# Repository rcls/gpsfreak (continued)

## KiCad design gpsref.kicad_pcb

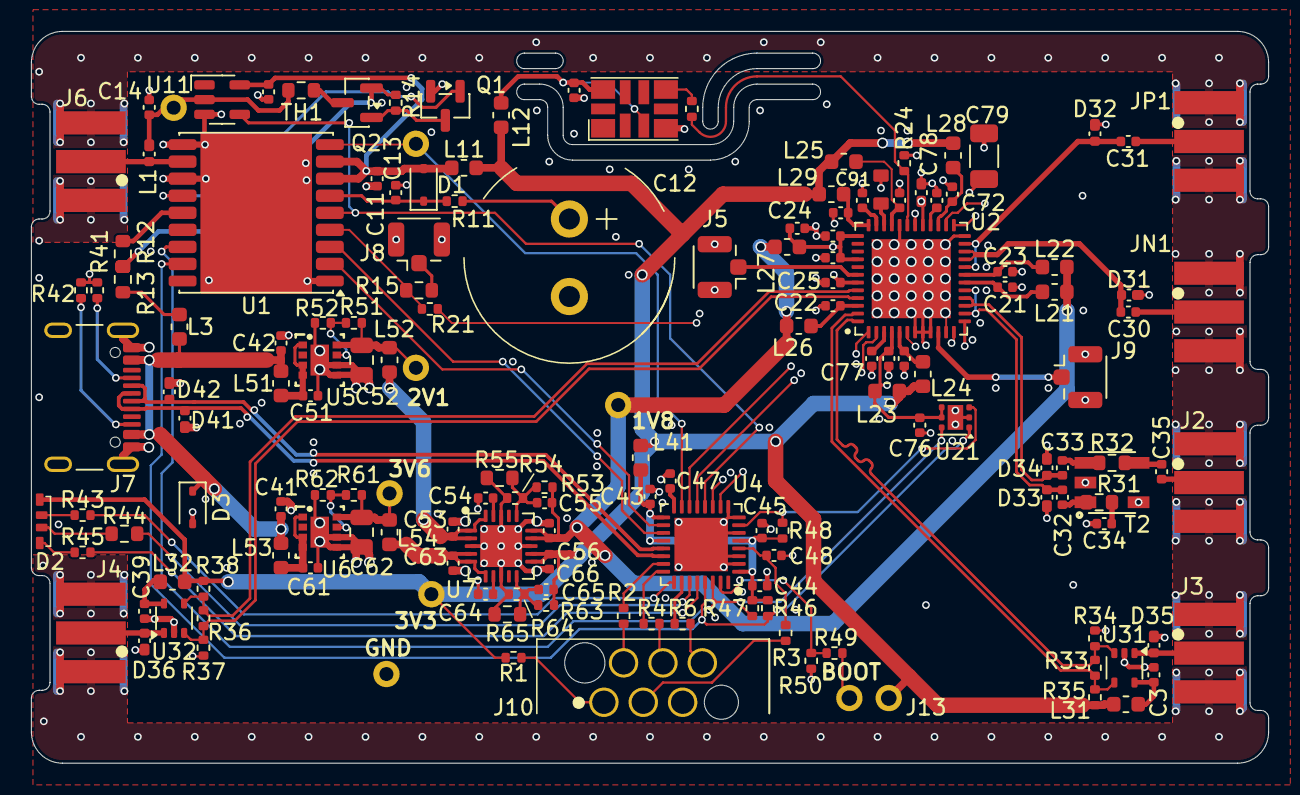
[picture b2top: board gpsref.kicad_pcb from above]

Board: 4 copper layers, 79.8 x 47.2 mm, 158 parts (0 on the bottom side), 102 nets.

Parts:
C3, C11, C21, C22, C23, C24, C29, C39, C43, C51, C53, C56, C61, C63, C66, C71, C72, C73, C74, C75, C77, C91, C93: 10u; C_0402_1005Metric
C12: .47F; CP_Radial_D13.5mm_P5.00mm
C13, C14, C15, C25, C27, C28, C30, C31, C32, C33, C35, C44, C45, C54, C64, C76: 0u1; C_0402_1005Metric
C34: 22p; C_0402_1005Metric
C41, C42: 1u; C_0402_1005Metric
C47: 4u7; C_0402_1005Metric
C48, C55, C65: 10n; C_0402_1005Metric
C52, C62: 47u; C_0805_2012Metric
C78: 10n; C_0402_1005Metric_Pad0.74x0.62mm_HandSolder
C79: 470n; C_1206_3216Metric
C92: 0u1; C0704
D1: 1N4148WS; D_SOD-323
D2: LED_GBAR; LED-QPLB615-RGB
D3: 5V6; D_SOD-323
D31, D32, D33, D34, D35, D36, D41, D42: D_TVS; HHS_0402
J2, J3, J4, J6: SMA; SMA_EdgeMount
J5, J8, J9: U.Fl; U.FL_Hirose_U.FL-R-SMT-1_Vertical
J7: USB_C_Receptacle_16P; USB_C_Receptacle_GCT_USB4105-xx-A_16P_TopMnt_Horizontal
J10: Skedd; Skedd6
J13: Boot; PinHeader_1x02_P2.54mm_Vertical
JN1: SMA; SMA_EdgeMount
JP1: SMA; SMA_EdgeMount
L1: 100n; HHS_0402
L3, L11, L12, L21, L22, L23, L24, L25, L26, L27, L28, L29, L31, L32, L41, L51, L52, L53, L54: 220; L_0603_1608Metric
Q1: AO3400A; SOT-23
Q2: AO3401A; SOT-23
R1, R2, R3, R4, R6, R11, R21, R23, R24, R33, R36, R49: 100; R_0402_1005Metric
R12, R13, R15, R32: 0; R_0603_1608Metric
R14, R34, R35, R37, R38, R50: 100k; R_0402_1005Metric
R31: 50; R_0603_1608Metric
R41, R42, R64: 5k1; R_0402_1005Metric
R43, R45: 1k; R_0402_1005Metric
R44: 2k7; R_0603_1608Metric
R46, R47, R48: 10k; R_0402_1005Metric
R51: 39k; R_0402_1005Metric
R52: 24k; R_0402_1005Metric
R53: 8k2; R_0402_1005Metric
R54: 7k5; R_0402_1005Metric
R55: 51k; R_0603_1608Metric
R61: 200k; R_0402_1005Metric
R62: 56k; R_0402_1005Metric
R63: 15k; R_0402_1005Metric
R65: 82k; R_0603_1608Metric
T2: MABA-010247-2R1250; XFMR_MABA-007159-000000
TH1: 220mA; R_0603_1608Metric
TP1, TP2, TP3, TP4, TP5, TP6, TP7: TestPoint_Probe; TestPoint
U1: MAX-M10S; ublox_MAX
U2: LMK05318BRGZR; QFN-48-1EP_7x7mm_P0.5mm_EP5.1x5.1mm
U3: TG5032CGN; QFN10_TG5032CGN 40.0000M-CAGHNA0_EPS
U4: STM32H503KBUx; QFN-32-1EP_5x5mm_P0.5mm_EP3.45x3.45mm
U5, U6: TPS82084SIL; SIL0008C_SMD_NV
U7: TPS7A8801RTJR; QFN-20-1EP_4x4mm_P0.5mm_EP2.7x2.7mm
U11: 74LVC1G07; SOT-23-5
U21: TMP117xxDRV; WSON-6-1EP_2x2mm_P0.65mm_EP1x1.6mm
U31, U32: TLV3601DCKR; SOT-353_SC-70-5

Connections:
+1V8: C55.1, C56.1, L21.1, L22.1, L26.1, L27.1, R53.1, TP6.1, U7.14 (OUT1), U7.15 (OUT1)
+3V3: C65.1, C66.1, D2.3 (A), J13.1, L11.1, L12.1, L23.1, L24.1, L25.1, L28.1, L29.1, L31.1, L32.1, L41.1, R1.2, R35.2, R38.2, R63.1, TP7.1, U7.11 (OUT2), U7.12 (OUT2)
/CPU/BOOT0: R49.2, R50.1, U4.31 (BOOT0)
/CPU/Blue: R43.2, U4.25 (USART3_RX)
/CPU/CC1: J7.A5 (CC1), R41.2
/CPU/CC2: J7.B5 (CC2), R42.2
/CPU/CPU_nRST: C48.1, R3.2, U4.4 (NRST)
/CPU/DBG_TX: R6.2, U4.26 (USART3_TX)
/CPU/Green: R44.2, U4.27 (PB4(NJTRST))
/CPU/Red: R45.2, U4.28 (PB5)
/CPU/SWCLK: R4.2, U4.24 (DEBUG_JTCK-SWCLK)
/CPU/SWDIO: R2.2, U4.23 (DEBUG_JTMS-SWDIO)
/CPU/USB_D+: D41.1 (A1), J7.A6 (D+), J7.B6 (D+), U4.22 (USB_DP)
/CPU/USB_D-: D42.1 (A1), J7.A7 (D-), J7.B7 (D-), U4.21 (USB_DM)
/CPU/VCPU: C43.1, C44.1, C45.1, L41.2, R46.2, R47.2, R48.2, U4.1 (VDD), U4.5 (VDDA), U4.17 (VDD), U4.20 (PA9)
/CPU/d3V3: J10.1, R1.1
/CPU/dBOOT: J13.2, R49.1
/CPU/dRST: J10.3, R3.1
/CPU/dSWC: J10.4, R4.1
/CPU/dSWD: J10.2, R2.1
/CPU/dTX: J10.6, R6.1
/Clocking/CAP_PLL1: C93.2, U2.28 (CAP_PLL1)
/Clocking/CAP_PLL2: C91.2, U2.35 (CAP_PLL2)
/Clocking/GPSCLKLO: R21.2, U2.6 (PRIREF_P)
/Clocking/LF1: C78.1, C79.1, U2.29 (LF1)
/Clocking/LF2: C92.1, U2.34 (LF2)
/Clocking/SecRef: J9.1 (In), U2.10 (SECREF_P)
/Clocking/VCC_XO: C29.1, L12.2, U3.3 (OE), U3.9 (VCC)
/Clocking/VDDO_01: C21.1, L21.2, U2.18 (VDDO_01)
/Clocking/VDDO_7: C22.1, L26.2, U2.46 (VDDO_7)
/Clocking/VDDO_23: C23.1, L22.2, U2.19 (VDDO_23)
/Clocking/VDDO_456: C24.1, C25.1, C27.1, C28.1, L27.2, U2.37 (VDDO_4), U2.40 (VDDO_5), U2.43 (VDDO_6)
/Clocking/VDDO_PLL2: C74.1, L29.2, U2.36 (VDD_PLL2)
/Clocking/VDDO_XO: C75.1, L25.2, U2.33 (VDD_XO)
/Clocking/VDD_DIG: C71.1, C76.1, L23.2, U2.4 (VDD_DIG), U2.12 (GPIO0), U21.4 (ADD0), U21.5 (V+)
/Clocking/VDD_IN: C73.1, L24.2, U2.5 (VDD_IN)
/Clocking/VDD_PLL1: C72.1, L28.2, U2.27 (VDD_PLL1)
/Clocking/XO: R23.1, U3.6 (OUT)
/Clocking/XO_P: R23.2, R24.2, U2.31 (XO_P)
/GPS/GPSin: J6.1 (In), L1.1, U1.11 (RF_IN)
/GPS/LNA_EN: Q1.1 (G), U1.13 (LNA_EN)
/GPS/VBCKP: C13.1, D1.1 (K), R11.2, U1.6 (V_BCKP)
/GPS/VCC_RF: R12.1, U1.14 (VCC_RF)
/GPS/VGPS: C11.1, C15.1, D1.2 (A), L11.2, U1.7 (VCC_IO), U1.8 (VCC), U11.5 (VCC)
/GPS/Vrf: Q2.2 (S), R12.2, R13.2, R14.1
/GPS/VrfSW: C14.1, L1.2, TH1.1, TP2.1, U11.2
/Outputs/Ext2: C35.1, R32.2, T2.4
/Outputs/Ext3: D35.1 (A1), J3.1 (In), U31.1
/Outputs/Ext4: D36.1 (A1), J4.1 (In), U32.1
/Power/2V1: C52.1, L52.1, R51.1, TP4.1, U5.8 (VOUT)
/Power/3V6: C62.1, L54.1, R61.1, TP5.1, U6.8 (VOUT)
/Power/Fb3V3: C65.2, R63.2, R64.1, R65.1, U7.10 (FB2)
/Power/Fb21: R51.2, R52.1, U5.7 (FB)
/Power/Fb36: R61.2, R62.1, U6.7 (FB)
/Power/FbCG18: C55.2, R53.2, R54.1, R55.1, U7.16 (FB1)
/Power/In1V8: C53.1, L52.2, U7.1 (IN1), U7.2 (IN1), U7.20 (EN1)
/Power/In2V1: C51.1, L51.2, U5.1 (EN), U5.3 (VIN), U5.4 (VIN)
/Power/In3V3: C63.1, L54.2, U7.4 (IN2), U7.5 (IN2), U7.6 (EN2)
/Power/In3V6: C61.1, L53.2, U6.1 (EN), U6.3 (VIN), U6.4 (VIN)
ALERT: R48.1, U4.7 (PA1), U21.3 (ALERT)
CPU2GPS: U1.3 (RXD), U4.19 (USART2_TX)
EXTINT: U1.5 (EXTINT), U4.12 (PA6), U11.4
FDEC: U2.2 (_FDEC), U4.13 (TIM2_CH3)
FINC: U2.30 (_FINC), U4.11 (TIM2_CH1)
GND: C3.2, C11.2, C12.2, C13.2, C14.2, C15.2, C21.2, C22.2, C23.2, C24.2, C25.2, C27.2, C28.2, C29.2, C34.1, C39.2, C41.1, C42.1, C43.2, C44.2, C45.2, C47.2, C48.2, C51.2, C52.2, C53.2, C54.2, C56.2, C61.2, C62.2, C63.2, C64.2, C66.2, C71.2, C72.2, C73.2, C74.2, C75.2, C76.2, C77.1, C78.2, C79.2, C91.1, C92.2, C93.1, D3.2 (A), D31.2 (A2), D32.2 (A2), D33.2 (A2), D34.2 (A2), D35.2 (A2), D36.2 (A2), D41.2 (A2), D42.2 (A2), J2.2 (Ext), J3.2 (Ext), J4.2 (Ext), J5.2 (Ext), J6.2 (Ext), J7.A1 (GND), J7.A12 (GND), J7.B1 (GND), J7.B12 (GND), J7.S1 (SHIELD), J8.2 (Ext), J9.2 (Ext), J10.5, JN1.2 (Ext), JP1.2 (Ext), Q1.2 (S), R24.1, R34.1, R37.1, R41.1, R42.1, R50.2, R52.2, R54.2, R55.2, R62.2, R64.2, R65.2, T2.2, T2.5, TP3.1, U1.1 (GND), U1.10 (GND), U1.12 (GND), U2.7 (PRIREF_N), U2.8 (REFSEL), U2.9 (HW_SW_CTRL), U2.11 (SECREF_N), U2.24 (GPIO1), U2.32 (XO_N), U2.49 (GND), U3.4 (GND), U4.2 (PC14), U4.3 (PC15), U4.6 (PA0), U4.8 (PA2), U4.9 (PA3), U4.33 (VSS), U5.5 (GND), U5.6 (GND), U5.9 (PAD), U6.5 (GND), U6.6 (GND), U6.9 (PAD), U7.3 (GND), U7.8 (SS_CTRL2), U7.13 (GND), U7.18 (SS_CTRL1), U7.21 (GND), U11.3 (GND), U21.2 (GND), U21.7 (GND), U31.2 (V-), U32.2 (V-)
GPS2CPU: U1.2 (TXD), U4.18 (USART2_RX)
GPSCLK: R15.1, R21.1, U1.4 (TIMEPULSE)
GPS_nRST: TP1.1, U1.9 (~RESET), U4.15 (PB1)
I2C_SCL: R46.1, U1.17 (SCL), U2.26 (SCL), U4.29 (I2C1_SCL), U21.1 (SCL)
I2C_SDA: R47.1, U1.16 (SDA), U2.25 (SDA), U4.30 (I2C1_SDA), U21.6 (SDA)
unnamed: C12.1, R11.1
unnamed: C32.2, R31.2, T2.1
unnamed: C33.2, R32.1, T2.3
unnamed: C34.2, R31.1
unnamed: D2.2 (BK), R43.1
unnamed: D2.1 (GK), R44.1
unnamed: D2.4 (RK), R45.1
unnamed: C35.2, J2.1 (In)
unnamed: J8.1 (In), R15.2
unnamed: C30.2, JN1.1 (In)
unnamed: C31.2, JP1.1 (In)
unnamed: L3.2, R13.1
unnamed: Q1.3 (D), Q2.1 (G), R14.2
unnamed: Q2.3 (D), TH1.2
unnamed: C77.2, U2.3 (CAP_DIG)
unnamed: C47.1, U4.16 (VCAP)
unnamed: C54.1, U7.19 (NR_SS1)
unnamed: C64.1, U7.7 (NR_SS2)
unnamed: C3.1, L31.2, U31.5 (V+)
unnamed: C39.1, L32.2, U32.5 (V+)
OUT1_N: C30.1, D31.1 (A1), U2.21 (OUT2_N), U2.22 (OUT3_N)
OUT1_P: C31.1, D32.1 (A1), U2.20 (OUT2_P), U2.23 (OUT3_P)
OUT2_N: C33.1, D34.1 (A1), U2.15 (OUT0_N), U2.16 (OUT1_N)
OUT2_P: C32.1, D33.1 (A1), U2.14 (OUT0_P), U2.17 (OUT1_P)
OUT3_N: R33.2, R35.1, U2.47 (OUT7_N), U31.4 (-)
OUT3_P: R33.1, R34.2, U2.48 (OUT7_P), U31.3 (+)
OUT4_N: R36.2, R38.1, U2.44 (OUT6_N), U32.4 (-)
OUT4_P: R36.1, R37.2, U2.45 (OUT6_P), U32.3 (+)
OUT5: J5.1 (In), U2.42 (OUT5_P)
PDN: U2.13 (~PD), U4.10 (PA4)
STATUS0: U2.1 (STATUS0), U4.14 (PB0)
VBus: C41.2, C42.2, D3.1 (K), J7.A4 (VBUS), J7.A9 (VBUS), J7.B4 (VBUS), J7.B9 (VBUS), L3.1, L51.1, L53.1

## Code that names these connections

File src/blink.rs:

#![cfg_attr(target_os = "none", no_std)]
#![cfg_attr(target_os = "none", no_main)]
#![deny(warnings)]
#![allow(internal_features)]
#![allow(unpredictable_function_pointer_comparisons)]
#![feature(const_clone, const_cmp, const_default,const_index, const_trait_impl)]
#![feature(derive_const)]
#![feature(format_args_nl)]
#![feature(link_llvm_intrinsics)]
// #![feature(negative_impls)]
// #![allow(incomplete_features)]
// #![feature(specialization)]
// #![feature(with_negative_coherence)]

mod command;
mod cpu;
mod dma;
mod gps_uart;
mod i2c;
#[macro_use]
mod uart_debug;
mod usb;
#[macro_use]
mod utils;
mod vcell;

#[allow(non_snake_case)]
mod clock_config;

/// I²C address of the LMK05318(B).
const LMK05318: u8 = 0xc8;

/// I²C address of the TMP117.  ADD0 on the TMP117 connects to 3V3.
const TMP117: u8 = 0x92;

pub fn main() -> ! {
    let gpioa = unsafe {&*stm32h503::GPIOA::ptr()};
    let gpiob = unsafe {&*stm32h503::GPIOB::ptr()};
    let rcc   = unsafe {&*stm32h503::RCC  ::ptr()};

    rcc.AHB2ENR.modify(|_,w| w.GPIOAEN().set_bit().GPIOBEN().set_bit());

    cpu::init();

    uart_debug::init();

    command::init();

    i2c::init();
    usb::init();
    if true {gps_uart::init();}

    // FIXME - this races with interrupts using debug!
    dbgln!("Debug is up!");

    cpu::maybe_enter_dfu();

    if false {gps_uart::gps_reset();}

    // Set the SYSTICK handler priority.
    let scb = unsafe {&*cortex_m::peripheral::SCB::PTR};
    // In the ARM docs, this is the high byte of SHPR3 (0xE000ED20), so byte
    // address 0xE000ED23.
    link_assert!(&scb.shpr[11] as *const _ as usize == 0xe000ed23);
    unsafe {scb.shpr[11].write(cpu::interrupt::PRIO_APP)};
    unsafe {scb.cpacr.write(0x00f00000)};

    // Systick counts at 20MHz.
    unsafe {
        let syst = &*cortex_m::peripheral::SYST::PTR;
        syst.rvr.write(0xffffff);
        syst.cvr.write(0xffffff);
        syst.csr.write(3);
    }

    // LMK05318b PDN pin is on PA4.
    gpioa.BSRR.write(|w| w.BS4().set_bit());
    gpioa.MODER.modify(|_,w| w.MODE4().B_0x1());

    // PB1 is the GPS reset.
    gpiob.BSRR.write(|w| w.BS1().set_bit());
    gpiob.MODER.modify(|_,w| w.MODE1().B_0x1());

    // Setup the oscillator.
    if false {
        let r = clock_setup();
        dbgln!("Clock setup result = {r:?}");
    }

    // Blue/red/green are PA1,2,3.
    gpioa.BSRR.write(|w| w.bits(0xe));
    gpioa.MODER.modify(|_,w| w.MODE1().B_0x1().MODE2().B_0x1().MODE3().B_0x1());

    // EN_REF2 = PB5, deassert high
    // EN_OUT4 = PB4, assert low
    // nEN_OUT3 = PB8, assert low
    let gpiob = unsafe {&*stm32h503::GPIOB::ptr()};
    gpiob.BSRR.write(|w| w.BS4().set_bit().BR5().set_bit().BR8().set_bit());
    gpiob.MODER.modify(|_,w| w.MODE4().B_0x1().MODE5().B_0x1().MODE8().B_0x1());

    loop {
        cpu::WFE();
    }
}

fn systick_handler() {
    let gpioa = unsafe {&*stm32h503::GPIOA::ptr()};
    const NEXT: [u8; 8] = [0xe, 4, 8, 0xa, 0, 0xc, 2, 0x6];
    let led = NEXT[gpioa.ODR().read().bits() as usize >> 1 & 7];
    gpioa.BSRR.write(|w| w.bits(0xe0000 + led as u32));

    let mut temp: i16 = 0;
    if let Ok(_) = i2c::read_reg(TMP117, 0, &mut temp).wait() {
        let temp = i16::from_be(temp);
        dbgln!("Temp {temp:#x} {}", temp as i32 * 100 / 128);
    }
    else {
        dbgln!("Temp read fail");
    }
}

fn clock_setup() -> i2c::Result {
    for block in clock_config::REG_BLOCKS {
        i2c::write(LMK05318, block).wait()?;
    }
    // Read R12...
    i2c::write(LMK05318, &[0u8, 12]).wait()?;
    let mut r12 = 0u8;
    i2c::read(LMK05318, &mut r12).wait()?;
    // Write back with PLL cascade and reset.
    i2c::write(LMK05318, &[0u8, 12, r12 | 0x12]).wait()?;
    // Write back with PLL cascade.
    i2c::write(LMK05318, &[0u8, 12, r12 | 0x02]).wait()?;

    Ok(())
}

#[used]
#[unsafe(link_section = ".vectors")]
pub static VECTORS: cpu::VectorTable = {
    let mut vtor = cpu::VectorTable::default();
    vtor.systick = systick_handler;
    *vtor.debug().usb().gps_uart().i2c()
};

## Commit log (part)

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2025-08-07 Getting there with the schematic
2025-08-08 Schematic is basically feature complete
2025-08-08 Rename
2025-08-09 Sorting out the part placement....
2025-08-09 First round of component distribution
2025-08-10 Placement looks sane.
2025-08-11 Routing well underway
2025-08-11 Supercap is back
2025-08-12 Down to the dregs and clean-ups.
2025-08-12 Add a U.Fl connector for fun.
2025-08-12 DRC clean-up. Only silk-screen noise left.
2025-08-12 Redo the secondary reference termination.
2025-08-12 Squeeze in a connector to break out GPS.
2025-08-12 Tweak positioning.
2025-08-13 Silkscreen passes DRC. Also we renumbered everything.
2025-08-13 Sorting out part number assignments.
2025-08-13 Final fixes. Ordered.
2025-08-13 Various end and breakout boards
2025-08-14 Break-out and end boards as ordered
2025-08-17 Submodule
2025-08-17 Temporary push
2025-08-26 Change the programming connector.
    Change the SMA footprint to match narrow ones.
2025-08-26 Tidy up pinout.
2025-08-26 Ready for respin.
2025-09-02 WIP on the USB
2025-09-11 Littles
2025-09-14 Enumerates. I hate USB.
2025-09-15 Tweaks. In device mode, CHEP doesn't store USB address.
2025-09-19 Bring up the PLL.
    Lots of rearrangements.
    A really hacky GPS serial relay to debug.
2025-09-21 Getting there with USB CDC ACM.
    Need to handle setup OUT data.
    I still hate USB. I hate CDC even more.
2025-09-21 Re-arrange setup handling to prep for setup OUT.
2025-09-22 Rearrange to use submodules properly.
    The infrastructure for setup data OUT is there, just need to use it.
2025-09-22 Getting there with the data transfer.
    setup with data out still has a problem.
2025-09-23 Seems reliable now...
2025-09-24 I²C is up.
2025-09-25 Clock gen runs, plus DFU entry.
2025-09-25 Remove the HW double buffering support, it's useless.
    We just flip the buffer descriptors instead, which is easier and
    just as fast.
2025-09-25 Rearrange a bit.
2025-09-26 Minor updates to USB handling.
2025-09-26 Fix-up I2C NACK handling.
2025-09-29 Commands over USB are going.
2025-09-29 Touch up the python code
2025-09-29 License info
2025-09-29 LMK05318B document scraping
2025-09-30 Minor adjustments
2025-10-02 compiler_fence doesn't work how I expected. Use a combination of volatile reads and dummy asm instead.
2025-10-02 Spell fix.
2025-10-04 Support write-read I2C transactions.
2025-10-04 Reduce the Nack payload to just the error code.
2025-10-06 Major updates to the python scripts
2025-10-06 Turn a couple of scripts into real programs
2025-10-06 Reorganise the python scripts into something of a module structure.
2025-10-06 Regenerate the register pickle
2025-10-08 Getting the LMK tooling sorted a bit.
2025-10-09 Integrate LMK planning into the tool.
2025-10-09 Tweak numbering.
2025-10-09 Frequency planning upload works. There are still some magic undocumented registers that influence the output.
2025-10-10 Output drive configuration.
2025-10-10 More commands
2025-10-10 Simplify the message format.
2025-10-10 Integrate upload-tcs.
2025-10-11 Support for firmware being piggy in the middle.
    Add peek/poke commands.
2025-10-11 Add gps config 'changes' command
2025-10-11 It's not a blinky any more.
2025-10-11 Memory CRC message support. Tidy up
2025-10-12 Flash commands.
2025-10-12 Tighten up python typing.
2025-10-12 First cut of config provisioning code.
2025-10-12 First cut of provisioning working
2025-10-13 UBlox provisioning appears to work. Fingers crossed.
2025-10-13 Compute device frequencies.
    Various updates.
2025-10-13 Integrate the clock utils into the main tool
2025-10-13 Integrate GPS commands into the top level utility.
2025-10-14 More updates to the python.
    Dance around the errata a bit more.
2025-10-14 Tidy-ups.
2025-10-14 Do the serial comms via raw USB by default.
    Also, finally just remove the ACM CDC serial baud-rate setting, and fake that
    instead.
2025-10-14 Config saving in main app.
2025-10-15 Bug fix and overclock.
2025-10-16 Hook in LEDs. Just triggered off commands for now
2025-10-17 Blue LED blinks on all USB activity.
2025-10-17 Handle status flags when setting a frequency plan:
    Control the PLL2 LOL masking. Force a status update after uploading the new
    plan.
    Add a status command to print all the LOL flags.
    Various other tidy-ups.
2025-10-18 Red v. green status LED.
2025-10-18 Top level save, plus help updates.
2025-10-18 Allow attribute access for LMK05318b registers.
    Help updates.
2025-10-18 Simplify config save & use attributes.
2025-10-18 Cope with unsolicited UBX messages. Add a basic GPS status command.
2025-10-18 Add some undocumented LMK05318b registers.
2025-10-19 Implement output oriented drive selection.
    Improvements to argparse handling.
2025-10-20 Inexact low frequency planning.
2025-10-20 Minor tidy up.
2025-10-20 Split up PLL planning.
2025-10-21 More refactoring of planning, prep for pll1.
2025-10-21 Switch clock status line to status0.
2025-10-21 Schematic updates for revision mostly done.
2025-10-23 Cooked output drive.
2025-10-23 Use impedance matching baluns.
2025-10-23 Put the two long differential lines on the front.
2025-10-23 Routing basically done.
2025-10-23 DRC clean-up.
2025-10-23 Skedd connector is back.
    Route I2C to GPS and hook in the alert line.
2025-10-24 Route extint.
2025-10-24 Nix a DRC error.
2025-10-24 Add bias resistors to comparators.
2025-10-24 Fatten up power traces.
2025-10-25 Simplify CMOS output structure.
2025-10-25 Remove zombie fields.
2025-10-28 Manufacturing updates.
2025-10-29 LED refactor.
2025-10-29 Better default inference.
2025-10-29 Various simplifications and tidy-ups.
2025-10-30 First cut of DPLL planning
2025-10-31 Simplify, and better DPLL brute force.
2025-11-01 Minor updates and fixes.
2025-11-01 Minor refactoring / restructure
2025-11-01 Rename schematic
2025-11-01 Various dangling footprints
2025-11-01 Python typing updates. Using pyright.
2025-11-01 One more field from the datasheet
2025-11-01 Unify the live and planned frequency reporting.
2025-11-01 Remove some debug prints.
2025-11-02 Capitalise register names. Simplify the scraping script.
    Add a 'freak clock dump' command.
2025-11-02 Python backwards compatibility
2025-11-02 Pass pyright with strict.
2025-11-02 Just ignore the lack of stub files for pyusb, generated ones are useless anyway.
2025-11-02 Pass pyrefly checks also.
2025-11-03 Un-hardwire the reference frequency.
2025-11-03 Update LED handling for board variants.
2025-11-03 Print plans from the python structures instead of the config blob.
    Implement a function to reverse engineer the config blob.
2025-11-03 Make reporting gps config changes more flexible.
2025-11-04 Minor updates.
2025-11-04 Documentation update
2025-11-04 Add a heaps more fields from TICS/Pro
    Documentation and unittest updates.
2025-11-11 Updated register definitions doc (rev D)
2025-11-11 Minor python updates
2025-11-11 Make sure the status LED code doesn't spin at start-up.
2025-11-11 Minor planning updates.
2025-11-12 SUpport for get/set name and command line selection of device.
    Also, touch up selection of even dividers.
2025-11-14 Add command for initial configuration of device.
2025-11-14 Enlarge the exposed pad under the LMK chip to 11×7 mm.
    Also change the DNP flags to avoid the balun by default.
2025-11-15 Make all the LED resistors 0603 & adjust values.
    Move the LED inwards so it doesn't overhang.
2025-11-15 Use a plated hole for the LED panel opening
2025-11-15 Remove the strap resistor on the GPS timepulse U.Fl connector.
2025-11-16 Copper fill on both sides of end-out also.
2025-11-16 Tiny layout tweaks.
2025-11-16 Take the USB serial number from the assigned device name.
2025-11-16 Add some more TICS files. Change the default BW to 0.3Hz.
2025-11-17 Use a less squatty USB id.
2025-11-18 When applying a frequency plan, update the lock-detection registers.
2025-11-18 Fix a unittest that regressed.
2025-11-18 Use a non-disasterous factorization algorithm.
2025-11-18 Minor tidy ups and fix a stupid bug.
2025-11-18 Shuffle things around a bit.
2025-11-20 Minor renames.
2025-11-20 Update default config.
2025-11-20 Maintain XO & PFD frequency in planning code.
2025-11-20 Little bug fix.
2025-11-20 A couple more command options.
2025-11-21 Update README. Minor updates and bug fixes.
2025-11-24 Avoid DPLL dividers too close to an integer.
2025-11-24 Some random analysis tools
2025-11-25 Fixup the test for near-integer DPLL dividers.
2025-12-03 Minor changes. Sync up I2C a bit.
2025-12-04 Use debug from stm-common
2025-12-04 Use stm-common vcell.
2025-12-05 Use stm-common I2C.
2025-12-05 Add a couple of images to the README
2025-12-05 Fixup commanding DFU entry.
2025-12-05 Less silly image sizes
2025-12-05 Start on abstracting out USB driver.
2025-12-05 Convert the control end-point to the abstract trait.
    Set-up handling could usefully be pulled back up though?
2025-12-05 And move towards isolation....
2025-12-05 Move out the CDC interupt endpoint also.
2025-12-06 Break out the main usb command handler.
2025-12-06 Turn the string table generation into a big macro
2025-12-06 Abstract out the USB control side.
2025-12-06 Move the application specific descriptors out from under 'usb'.
2025-12-06 Split the hardware descriptions.
2025-12-06 Abstract out various bits of USB initialization.
2025-12-06 Start making common into a proper crate.
2025-12-06 WIP abstracting out debug.
2025-12-06 Moving stuff into common.
2025-12-06 REady to go....
2025-12-06 Debug is in the common crate.
2025-12-06 Track changes to debug.
2025-12-06 Cratize i2c.
2025-12-06 More stuff goes to common.
2025-12-06 Remove redundant submodule
2025-12-06 USB has gone to common.
2025-12-06 ove USB application code back under usb
2025-12-06 Little commons.
2025-12-07 Don't include the stack allocation in BSS.
2025-12-07 Track I2C changes.
2025-12-07 Get rid of submodule.
2025-12-07 Reify debug meta-data.
2025-12-07 Share some interrupt setup code. Various rationalisation.
2025-12-08 Minor tidy-ups.
2026-01-24 Add PDFs of schematic and PCB.
2026-03-24 Add LCSC part numbers for a few items.
    Don't 'exclude from BOM' things we want to assemble.
2026-03-26 Tweaks to python scripts.
    Add part numbers for the LED and 470nF C0G capacitor.
2026-03-26 Update all the PCB footprints to match latest kicad.
    Use our own SC-70, the latest kicad footprint has oversized pads.
2026-03-26 Adjust the footprint of the RGB LED to make it closer to the datasheet.
2026-03-26 Instead, switch to a RGB LED footprint from Paul Elliot.
2026-03-26 Split each output onto it's own sheet.
    Makes it easier to mix'n'match output types for board spins.
2026-03-28 Touch up net names.
2026-04-15 Update to match latest rust nightly compiler.
2026-04-16 Add the two extra arguments to Generator for older python versions.
2026-04-16 I ran kicad10 so now all the schematics are kicad10.
2026-04-17 Use the correct wIndex for entering DFU.
2026-04-18 Make the LMK05318B reference input divider configurable.
2026-04-18 Make `freak info` work if the temperature sensor is not populated.
2026-04-27 Fix an off-by-one in the OUT7 divider calculation.
    The DIV1 divider-by-6, register value 5 is not usable, despite what the docs say.
2026-05-02 When reporting device frequencies with fixed (1<<24) denominator, report that correctly.
2026-05-02 Add command-line argument for the APLL1 frequency.
2026-06-07 Minor python clean-ups.
2026-06-07 Add commands for I2C access to the GPS unit.
    The hardware works. But should we expose this as a USB end-point instead?
2026-06-07 Make the LED timer bit width a compile time option.
    Avoid an unnecessary cast.
2026-06-07 Inconsequential board tidy-ups.
2026-06-07 Remove unused components around GPS power.
    (Ant. power switch & monitor, backup supercap.)
2026-06-13 FPGA in, layout mostly updated.
2026-06-20 More UBX items
2026-06-20 Add the FGPA page....
2026-06-20 Layout down
2026-06-20 Ordered.
2026-06-20 Pull-up on safe-boot. Juggle things a bit.
2026-06-20 Back to tps82084...
2026-06-20 Tidy up.
2026-06-25 Adjustments. Silk screen clearance.
2026-06-25 Adjust LED pattern - comms activity turns off others.
    Tidy up.
